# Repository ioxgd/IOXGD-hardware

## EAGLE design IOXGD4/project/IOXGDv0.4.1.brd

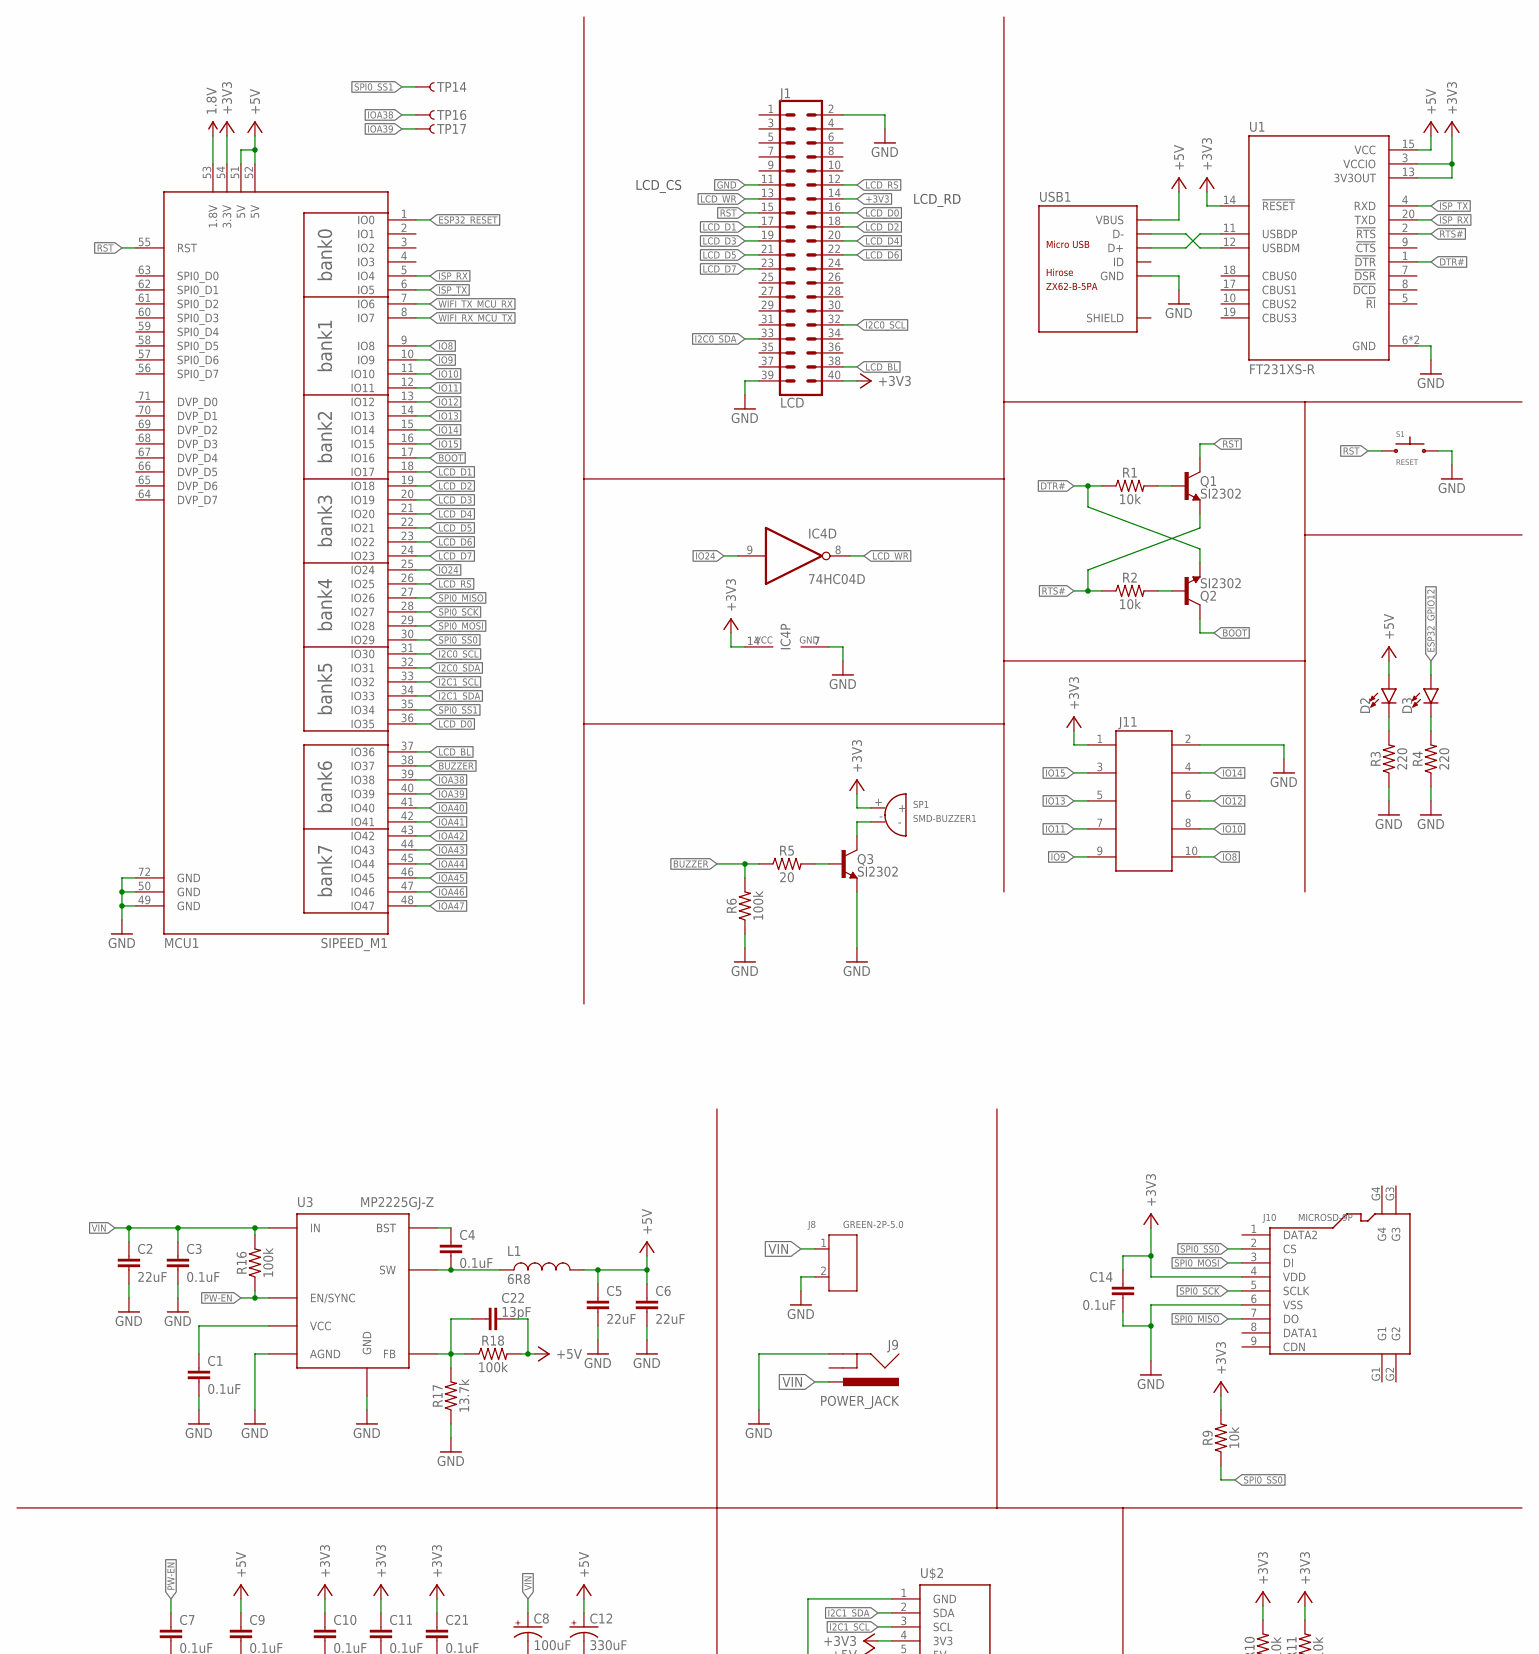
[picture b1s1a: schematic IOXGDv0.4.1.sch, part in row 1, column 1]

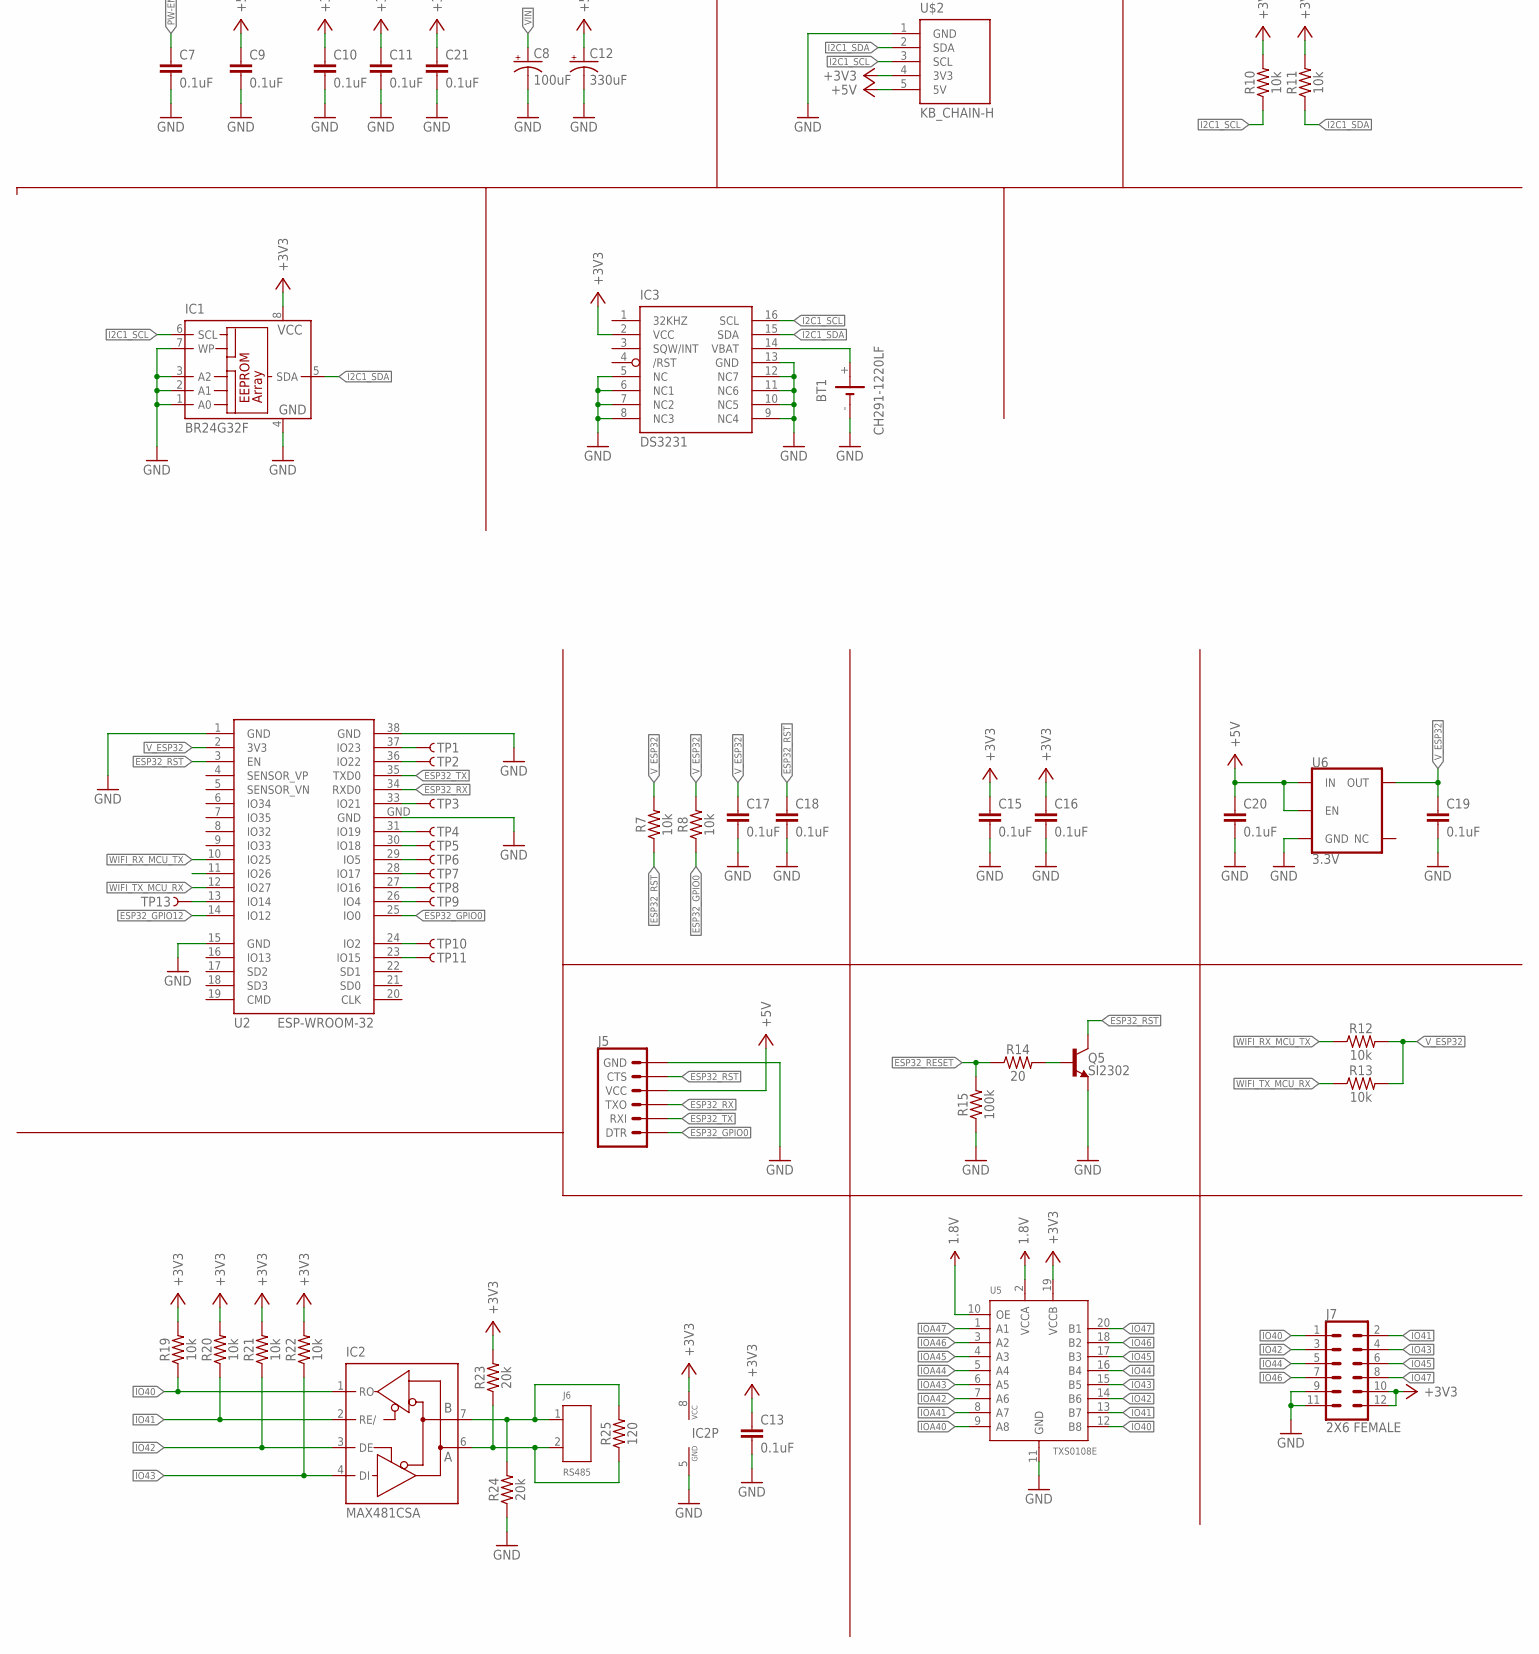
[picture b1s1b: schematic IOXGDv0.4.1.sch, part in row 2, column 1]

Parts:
BT1: CH291-1220LF
C1, C3, C4, C7, C9, C10, C11, C13, C14, C15, C16, C17, C18, C19, C20, C21: 0.1uF; 0603
C2: 22uF; 0805
C5, C6: 22uF; 0603
C8: 100uF; CPOL-RADIAL-2.5MM-6.5MM
C12: 330uF; CPOL-RADIAL-2.5MM-6.5MM
C22: 13pF; 0603
D2, D3: LED3MM; LED_3MM
IC1: BR24G32F; SO-08
IC2: MAX481CSA; SO08
IC3: DS3231/SO; SO16W
IC4: 74HC04D; SO14
J1: LCD; 2X20
J5: 6_PIN_SERIAL_TARGET; 1X06
J6: RS485; H2-5.0-10.5X8.0MM
J7: 2X6 FEMALE; 2X6
J8: GREEN-2P-5.0; H2-5.0-10.5X8.0MM
J9: POWER_JACK; POWER_JACK_PTH
J10: MICROSD-9P; MICRO-SD9+4P-SMD-16.1X14.5X1.85MM
J11: 612010235221
L1: 6R8; MCS0630SERIES
MCU1: SIPEED_M1; M1
Q1, Q2, Q3, Q5: SI2302; SOT23-3
R1, R2, R7, R8, R9, R10, R11, R12, R13, R19, R20, R21, R22: 10k; 0603
R3, R4: 220; 0603
R5, R14: 20; 0603
R6, R15, R16, R18: 100k; 0603
R17: 13.7k; 0603
R23, R24: 20k; 0603
R25: 120; 0603
S1: RESET; TC-020X
SP1: SMD-BUZZER1
TP1, TP2, TP3, TP4, TP5, TP6, TP7, TP8, TP9, TP10, TP11, TP13, TP14, TP16, TP17: TEST-POINT3X5; PAD.03X.05
U1: FT231XS-R; SOP63P599X175-20N
U2: ESP-WROOM-32
U3: MP2225GJ-Z; TSOT-23-8
U5: TXS0108E; TSSOP20-0.65-6.5X4.4MM
U6: 3.3V; SOT23-5
U$2: KB_CHAIN-H; JST5PIN
USB1: ZX62-B-5PA; MICRO-USB5+6P-SMD-0.65-AB

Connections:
1.8V: MCU1.53 (1.8V), U5.2 (VCCA), U5.10 (OE)
+3V3: C10.1, C11.1, C13.1, C14.1, C15.1, C16.1, C21.1, IC1.8 (VCC), IC2.8 (VCC), IC3.2 (VCC), IC4.14 (VCC), J1.14, J1.40, J7.10, J7.12, J10.4 (VDD), J11.1 (10), MCU1.54 (3.3V), R9.2, R10.2, R11.2, R19.2, R20.2, R21.2, R22.2, R23.2, SP1.+, U1.3 (VCCIO), U1.13 (3V3OUT), U1.14 (!RESET), U5.19 (VCCB), U$2.4 (3V3)
+5V: C5.1, C6.1, C9.1, C12.1 (+), C20.1, C22.2, D2.A, J5.4 (VCC), L1.P$2, MCU1.51 (5V), MCU1.52 (5V), R18.2, U1.15 (VCC), U6.1 (IN), U6.3 (EN), U$2.5 (5V), USB1.1 (VBUS)
A: IC2.6 (A), J6.2, R23.1, R25.1
B: IC2.7 (B), J6.1, R24.2, R25.2
BOOT: MCU1.17 (IO16), Q2.3 (C)
BUZZER: MCU1.38 (IO37), R5.1, R6.2
DTR#: Q2.2 (E), R1.1, U1.1 (!DTR)
ESP32_GPIO0: J5.1 (DTR), R8.1, U2.25 (IO0)
ESP32_GPIO2: TP10.P$1, U2.24 (IO2)
ESP32_GPIO4: TP9.P$1, U2.26 (IO4)
ESP32_GPIO5: TP6.P$1, U2.29 (IO5)
ESP32_GPIO12: D3.A, U2.14 (IO12)
ESP32_GPIO14: TP13.P$1, U2.13 (IO14)
ESP32_GPIO15: TP11.P$1, U2.23 (IO15)
ESP32_GPIO16: TP8.P$1, U2.27 (IO16)
ESP32_GPIO17: TP7.P$1, U2.28 (IO17)
ESP32_GPIO18: TP5.P$1, U2.30 (IO18)
ESP32_GPIO19: TP4.P$1, U2.31 (IO19)
ESP32_GPIO21: TP3.P$1, U2.33 (IO21)
ESP32_GPIO22: TP2.P$1, U2.36 (IO22)
ESP32_GPIO23: TP1.P$1, U2.37 (IO23)
ESP32_RESET: MCU1.1 (IO0), R14.1, R15.2
ESP32_RST: C18.1, J5.5 (CTS), Q5.3 (C), R7.1, U2.3 (EN)
ESP32_RX: J5.3 (TXO), U2.34 (RXD0)
ESP32_TX: J5.2 (RXI), U2.35 (TXD0)
GND: BT1.-, C1.2, C2.2, C3.2, C5.2, C6.2, C7.2, C8.2 (-), C9.2, C10.2, C11.2, C12.2 (-), C13.2, C14.2, C15.2, C16.2, C17.2, C18.2, C19.2, C20.2, C21.2, IC1.1 (A0), IC1.2 (A1), IC1.3 (A2), IC1.4 (GND), IC1.7 (WP), IC2.5 (GND), IC3.5 (NC), IC3.6 (NC1), IC3.7 (NC2), IC3.8 (NC3), IC3.9 (NC4), IC3.10 (NC5), IC3.11 (NC6), IC3.12 (NC7), IC3.13 (GND), IC4.7 (GND), J1.2, J1.11, J1.39, J5.6 (GND), J7.9, J7.11, J8.2, J9.GND, J10.6 (VSS), J11.2 (9), MCU1.49 (GND), MCU1.50 (GND), MCU1.72 (GND), Q3.2 (E), Q5.2 (E), R3.1, R4.1, R6.1, R15.1, R17.1, R24.1, S1.2, U1.6 (GND), U1.16 (GND), U2.1 (GND), U2.15 (GND), U2.38 (GND), U2.GND, U3.1 (AGND), U3.4 (GND), U5.11 (GND), U6.2 (GND), U$2.1 (GND), USB1.5 (GND)
I2C0_SCL: J1.32, MCU1.31 (IO30)
I2C0_SDA: J1.33, MCU1.32 (IO31)
I2C1_SCL: IC1.6 (SCL), IC3.16 (SCL), MCU1.33 (IO32), R10.1, U$2.3 (SCL)
I2C1_SDA: IC1.5 (SDA), IC3.15 (SDA), MCU1.34 (IO33), R11.1, U$2.2 (SDA)
IO8: J11.10 (1), MCU1.9 (IO8)
IO9: J11.9 (2), MCU1.10 (IO9)
IO10: J11.8 (3), MCU1.11 (IO10)
IO11: J11.7 (4), MCU1.12 (IO11)
IO12: J11.6 (5), MCU1.13 (IO12)
IO13: J11.5 (6), MCU1.14 (IO13)
IO14: J11.4 (7), MCU1.15 (IO14)
IO15: J11.3 (8), MCU1.16 (IO15)
IO24: IC4.9 (I), MCU1.25 (IO24)
IO40: IC2.1 (RO), J7.1, R19.1, U5.12 (B8)
IO41: IC2.2 (RE/), J7.2, R20.1, U5.13 (B7)
IO42: IC2.3 (DE), J7.3, R21.1, U5.14 (B6)
IO43: IC2.4 (DI), J7.4, R22.1, U5.15 (B5)
IO44: J7.5, U5.16 (B4)
IO45: J7.6, U5.17 (B3)
IO46: J7.7, U5.18 (B2)
IO47: J7.8, U5.20 (B1)
IOA38: MCU1.39 (IO38), TP16.P$1
IOA39: MCU1.40 (IO39), TP17.P$1
IOA40: MCU1.41 (IO40), U5.9 (A8)
IOA41: MCU1.42 (IO41), U5.8 (A7)
IOA42: MCU1.43 (IO42), U5.7 (A6)
IOA43: MCU1.44 (IO43), U5.6 (A5)
IOA44: MCU1.45 (IO44), U5.5 (A4)
IOA45: MCU1.46 (IO45), U5.4 (A3)
IOA46: MCU1.47 (IO46), U5.3 (A2)
IOA47: MCU1.48 (IO47), U5.1 (A1)
ISP_RX: MCU1.5 (IO4), U1.20 (TXD)
ISP_TX: MCU1.6 (IO5), U1.4 (RXD)
LCD_BL: J1.38, MCU1.37 (IO36)
LCD_D0: J1.16, MCU1.36 (IO35)
LCD_D1: J1.17, MCU1.18 (IO17)
LCD_D2: J1.18, MCU1.19 (IO18)
LCD_D3: J1.19, MCU1.20 (IO19)
LCD_D4: J1.20, MCU1.21 (IO20)
LCD_D5: J1.21, MCU1.22 (IO21)
LCD_D6: J1.22, MCU1.23 (IO22)
LCD_D7: J1.23, MCU1.24 (IO23)
LCD_RS: J1.12, MCU1.26 (IO25)
LCD_WR: IC4.8 (O), J1.13
unnamed: U1.11 (USBDP), USB1.3 (D+)
unnamed: U1.12 (USBDM), USB1.2 (D-)
unnamed: Q2.1 (B), R2.2
unnamed: Q1.1 (B), R1.2
unnamed: BT1.+, IC3.14 (VBAT)
unnamed: C1.1, U3.7 (VCC)
unnamed: D2.K (C), R3.2
unnamed: D3.K (C), R4.2
unnamed: Q3.3 (C), SP1.-
unnamed: Q3.1 (B), R5.2
unnamed: C4.1, U3.5 (BST)
unnamed: C4.2, L1.P$1, U3.3 (SW)
unnamed: C22.1, R17.2, R18.1, U3.8 (FB)
unnamed: Q5.1 (B), R14.2
PW-EN: C7.1, R16.1, U3.6 (EN/SYNC)
RST: J1.15, MCU1.55 (RST), Q1.3 (C), S1.1
RTS#: Q1.2 (E), R2.1, U1.2 (!RTS)
SPI0_MISO: J10.7 (DO), MCU1.27 (IO26)
SPI0_MOSI: J10.3 (DI), MCU1.29 (IO28)
SPI0_SCK: J10.5 (SCLK), MCU1.28 (IO27)
SPI0_SS0: J10.2 (CS), MCU1.30 (IO29), R9.1
SPI0_SS1: MCU1.35 (IO34), TP14.P$1
VIN: C2.1, C3.1, C8.1 (+), J8.1, J9.PWR, R16.2, U3.2 (IN)
V_ESP32: C17.1, C19.1, R7.2, R8.2, R12.2, R13.2, U2.2 (3V3), U6.5 (OUT)
WIFI_RX_MCU_TX: MCU1.8 (IO7), R12.1, U2.10 (IO25)
WIFI_TX_MCU_RX: MCU1.7 (IO6), R13.1, U2.12 (IO27)

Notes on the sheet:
LCD_CS
LCD_RD

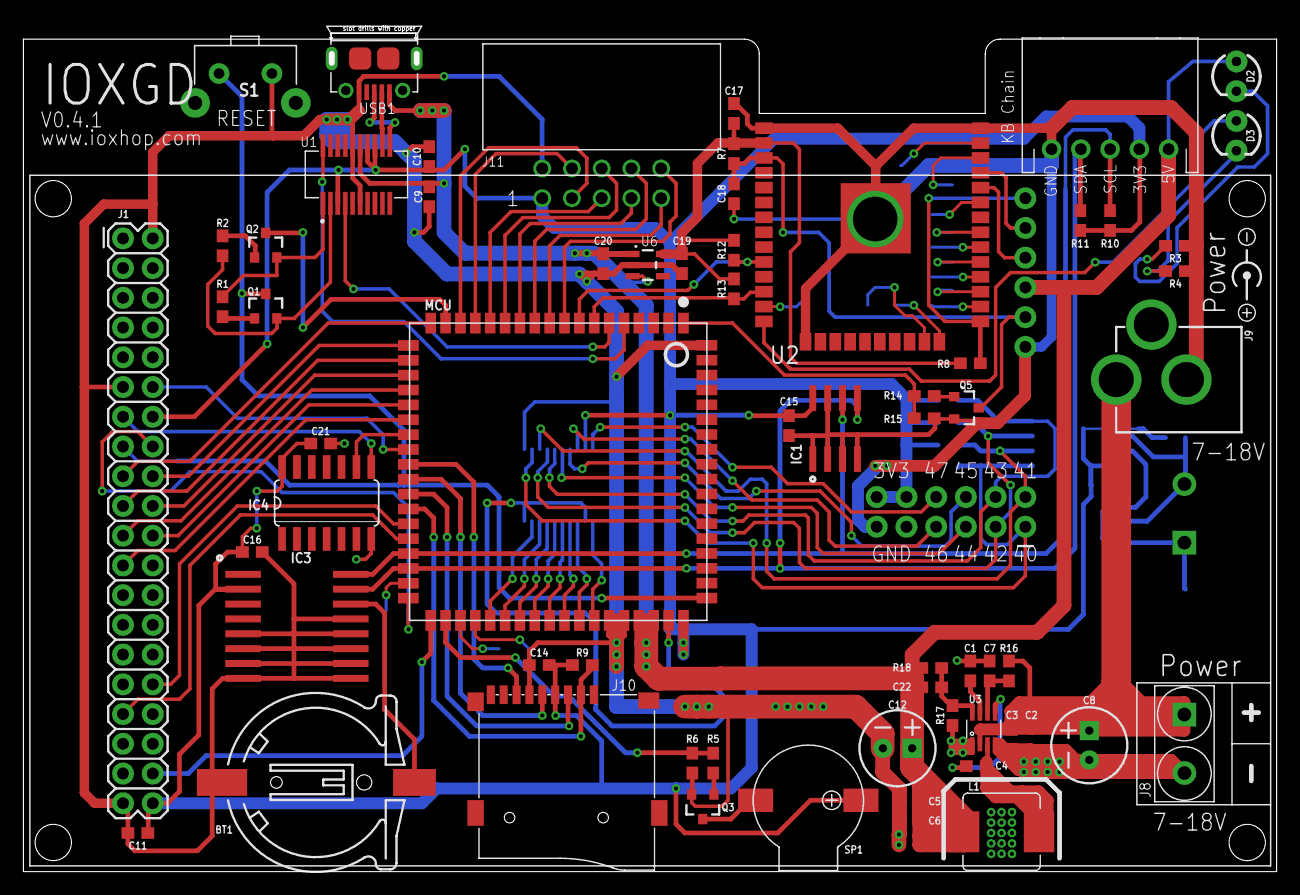
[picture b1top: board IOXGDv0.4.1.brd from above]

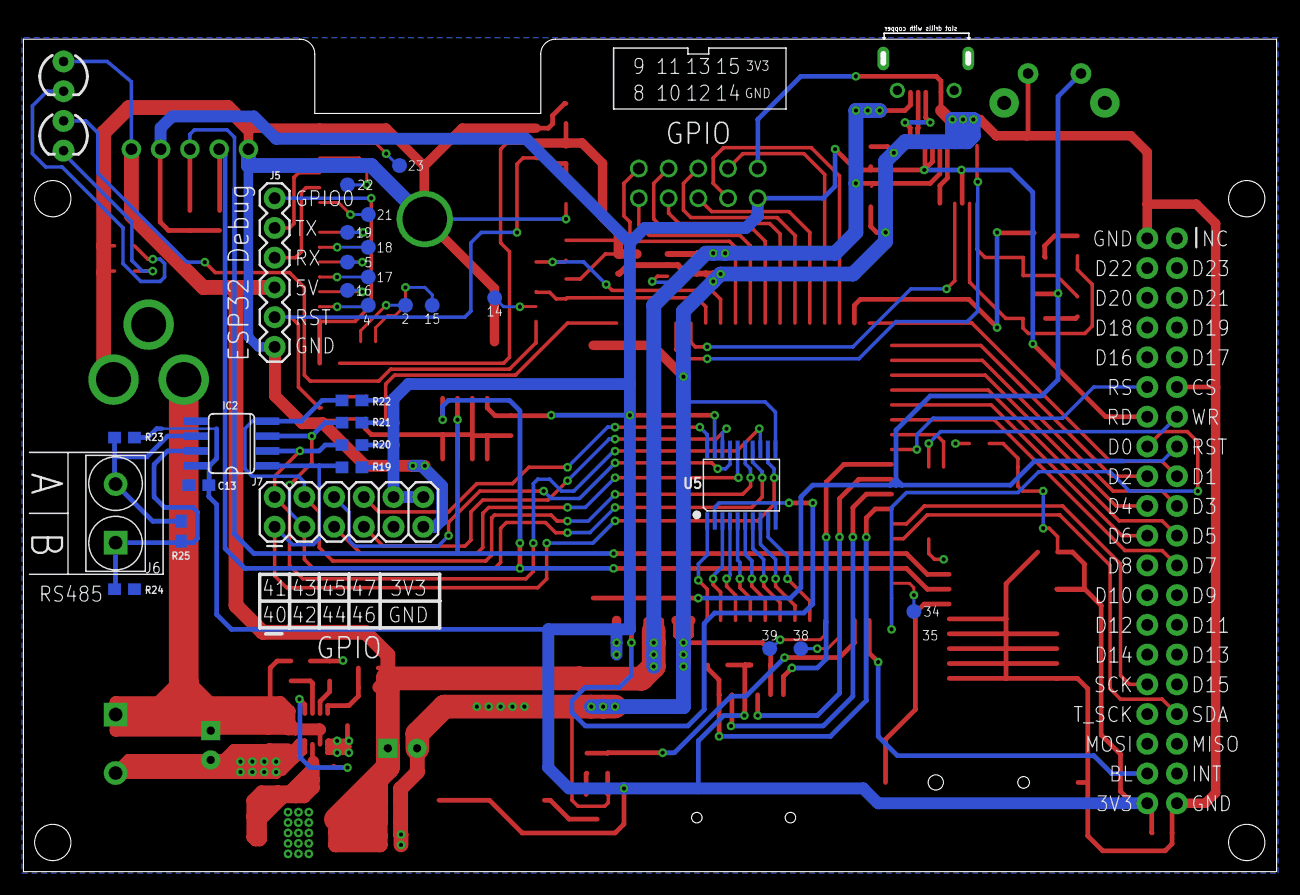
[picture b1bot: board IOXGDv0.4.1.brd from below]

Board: 2 copper layers, 106.6 x 72.0 mm, 92 parts (28 on the bottom side), 97 nets.

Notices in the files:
parts and their libraries:
SparkFun-Connectors: Licensing: Creative Commons ShareAlike 4.0 International - https://creativecommons.org/licenses/by-sa/4.0
esp322: Creative Commons Attribution-ShareAlike 4.0 International
Wurth_Elektronik_Electromechanic_Wire_to: Copyright: Würth Elektronik
